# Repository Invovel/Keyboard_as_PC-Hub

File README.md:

# Keyboard as PC Hub

## 当前产品基准 · RevC

[RevC 工程入口](docs/revc/README.md) · [差异审查](docs/revc/REVIEW.md) · [工作分工](docs/revc/PLAN.md) · [协作规范](AGENTS.md)。

冻结环形霍尔四键和独立 RGB、EC56 与独立屏幕下压、承力下壳、双马达、独立麦克风、浮动 USB-C 键盘公头，以及完整 Hub 和隔离口。右 MAG、左拨轮、现有五页固件与可选底置 Dock 继续纳入。现行工程从已核验的 116 封装修复板继承，当前保存板有 159 个封装。详见[真实四层铜、焊盘和钻孔证据](docs/revc/evidence/README.md)。**制造未放行。**

### RevC PCB 线路综合图

图源为保存板 `942accd835ab9017…`。内层覆铜另见[电源与地平面](docs/revc/evidence/PC_Hub_Inner_Planes.svg)。[查看 SVG 原图](docs/revc/evidence/PC_Hub_Pure_Circuit_Overview.svg) · [MAG-R 修改进度](docs/revc/pcb/MAG_R_PROGRESS.md)。

## R3.1 历史设计资料

**Desktop Control Hub · R3.1：Core＋可选下置Power Dock＋低功耗MAG附件。**

Core背部PC-C是唯一电脑上行，单线从电脑允许的VBUS预算取电，目标为不依赖Dock即可使用主体与键盘。Hub硬件转发USB外设数据，ESP32负责圆屏、旋钮、四键、音频和HID；Hub启动不应依赖ESP32固件。单线功耗、Hub配置与故障独立性尚未通过整机验证。

[R3.1 交接](docs/R3_1_CODEX_HANDOFF.md) · [历史差异与决策](docs/R3_1_DECISIONS.md) · [WP1/WP2 工程评审](docs/R3_1_ENGINEERING_REVIEW.md) · [当前开发入口](CODEX_START.md)

[补充讨论采用/放弃清单](docs/R3_1_SUPPLEMENT.md)：保留五键与104mm前部横条，补强Hub启动和Slider验证，早期双向供电/竖条/第二上行不混入当前设计。

**新增设计决定：[最右侧 ISO／DEBUG USB-A](docs/iso-debug-r3-1.md)。** PC-C候选中心移至X≈+64，ISO口X≈+91；由P6经独立USB2双下游Hub保留CTRL并增设隔离调试链路。首版采用隔离电源、集成限流/短路/防反灌保护、数据ESD和本地故障指示；精确计量留作后续选装。[候选材料表](hardware/electronics/iso-debug-candidate-bom.csv)不等于采购或保护能力认证。

[原理图摆位表](docs/iso-debug-schematic-placement-r3-1.md) · [A3摆位视图](design/drawings/iso-debug-schematic-placement-r3-1.svg) · [首版功能连接参考](design/drawings/iso-debug-minimal-schematic-r3-1.svg) · [Anatomy结构视图](design/visualization/iso-debug-anatomy.html) · [预览图](design/visualization/iso-debug-anatomy-preview.png)。当前仅确定原理图页内位置，未画导线或PCB；现有KiCad主工程尚未写入该页。

## R3.1 结构与接口

| 部位 | R3.1分工 |
| --- | --- |
| Core背部 | A1、A2、PC-C、最右侧ISO／DEBUG USB-A；PC-C唯一电脑上行，无Core POWER输入 |
| Core左侧 | FAST-C，目标10Gbps下游；实际供电按预算，不预先承诺3A |
| KBD / CTRL | 可调Type-C键盘公头 / 内部ESP32 USB2 Full-Speed HID |
| Core底部 | P4 Dock DATA＋独立PWR/CTRL预留，封装与开孔未定 |
| 可选下置Dock | Rev B：扩展Hub、外部PD受电、保护降压、单向给Core供电；没有第二电脑上行 |
| 两端MAG | 低速、低功耗8触点；五键及前部唯一横向触控条，不传高速USB/全机电流 |

逻辑下游P1=A1、P2=A2、P3=FAST、P4=DOCK、P5=KBD、P6=USB2分支至原CTRL与新ISO／DEBUG；这是架构分配，不是芯片物理引脚。USB7206C仍为候选，尚未证明Core单线工作能力。旧A3迁为Dock数据链路，POWER IN移至Dock；旧100W/46W单体预算仅保留为历史。

| 尺寸 | 候选值，mm |
| --- | --- |
| Core / PCB | 228×76、5°，前20/后26.65；PCB216×64×1.6 |
| 短四键 | 四片镜像，外端X=±84，两端各留30固定壳面；键面高0.3 |
| 感应中心 | (±65,±18)，保持原位 |
| 环 / 屏 / AA | Ø60 / Ø44.32 / Ø38.16；单边可见边框1.8 |
| 五键 / 横条 | 112×76一字五键；前部横条104×22×8，目标有效长90～96 |
| 底部Dock研究区 | 48×18功能区；8板间距和20高Dock包络均未冻结 |

新增[左右马达预留与PCB布局](hardware/pcb/references/core-haptic-placement-r3-1.md)：2026-10-22锁定[iPhone 7 Plus Taptic Engine](docs/haptic-iphone-7-plus.md)，按用户给定含耳50×12.5×2.6 mm设计，每侧装配区改为15×54×6 mm、长边沿Y，两端顶面保持完整留白。接线采用六测试焊盘最外侧两点接独立触觉驱动；[本轮原生执行记录](hardware/pcb/references/haptic-7plus-native-update.md)与[10月19日历史板图/DRC](hardware/pcb/exports/core-r3-1-haptic-study/README.md)分开保存。新板尚未接网/布线，不能打样。

## 原HTML持续更新

[原单文件HTML](design/visualization/hairline-keyboard-hub.html) · [使用与截图](design/visualization/README.md)。下载后离线打开；悬停主体展开、点击固定/复位，右侧五键及横条磁吸拆分。可选Dock只在主体展开时显示研究包络；默认Core不装Dock。GitHub README仅显示静态图。

[底部接口与侧剖](design/drawings/dock-interface-r3-1.svg) · [R3.1机械说明](hardware/enclosure/dimensions-r3-1.md) · [端口选型表](hardware/electronics/dock-port-selection.csv)

[ISO口与右马达、后孔空间关系](design/drawings/iso-debug-rear-study-r3-1.svg)：这是候选二维研究，开孔仍未冻结。

## 实物进展与文件分类

已运行主体：圆屏、触控页面、触摸板、USB键鼠/媒体HID、四键、按压输入、编码器与提示音；[实测历史](docs/body-core-bringup.md)保留原文。Touchpad延迟本轮不改。新增[INMP441代码](docs/microphone-inmp441.md)只编译，默认关闭，未接实物。输入按压通过不代表屏幕Z轴机械机构已完成。

| 分类 | 入口 | 状态 |
| --- | --- | --- |
| 固件 | [firmware](firmware/README.md) | 保留已运行GPIO与整合代码，本轮不改动/烧录 |
| 展示与图纸 | [design](design/README.md) | 原HTML、R3.1俯视/底视/剖面示意 |
| 机械 | [hardware/enclosure](hardware/enclosure/README.md) | R3.1参数/草模，未实体编译与装配验证 |
| PCB | [hardware/pcb](hardware/pcb/README.md) | 新增指定工程的R3.1布局草案与马达预留；未接网/布线，DRC未通过；R3载板保留历史 |
| 接口与接线 | [hardware/electronics](hardware/electronics/README.md) | 新接口目标与既有实物分开记录 |
| 镜像与证据 | [releases](releases/README.md)、[tests](tests/README.md) | 保留原镜像、许可和真实日志 |

尚未完成电源/Hub/Dock电路、连接器冻结、ERC、USB合规、闭壳温升或制造放行。新增布局已运行DRC但未通过；完整原理图与电气连接仍待完成。不做第二上行、双向大电流、手机高压PD输出、读卡、电池或竖触控条。

[目录规则](docs/repository-layout.md) · [本轮检查](tests/design/r3-1-review.md) · [R3历史尺寸](hardware/enclosure/dimensions-r3.md) · [旧单体供电方案](docs/desktop-power-dock.md) · [R2历史](hardware/enclosure/dimensions-r2.md)

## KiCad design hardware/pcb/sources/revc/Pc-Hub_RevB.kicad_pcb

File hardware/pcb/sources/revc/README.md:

# PC-Hub RevC KiCad 工作工程

打开 [Pc-Hub_RevB.kicad_pro](Pc-Hub_RevB.kicad_pro)。保留 KiCad 原文件名以维持工程及层级标识。本项目从 116 封装保存板 `3f082629954bdb488613209f4213198f4b84ce832a26fdd4af76abb786354d88` 派生。工程引用随项目提交的封装和符号库。

产品坐标、当前批次证据和制造门槛见 [RevC 入口](../../../../docs/revc/README.md)。生产投板须经过剩余的电气、几何及实体校验。

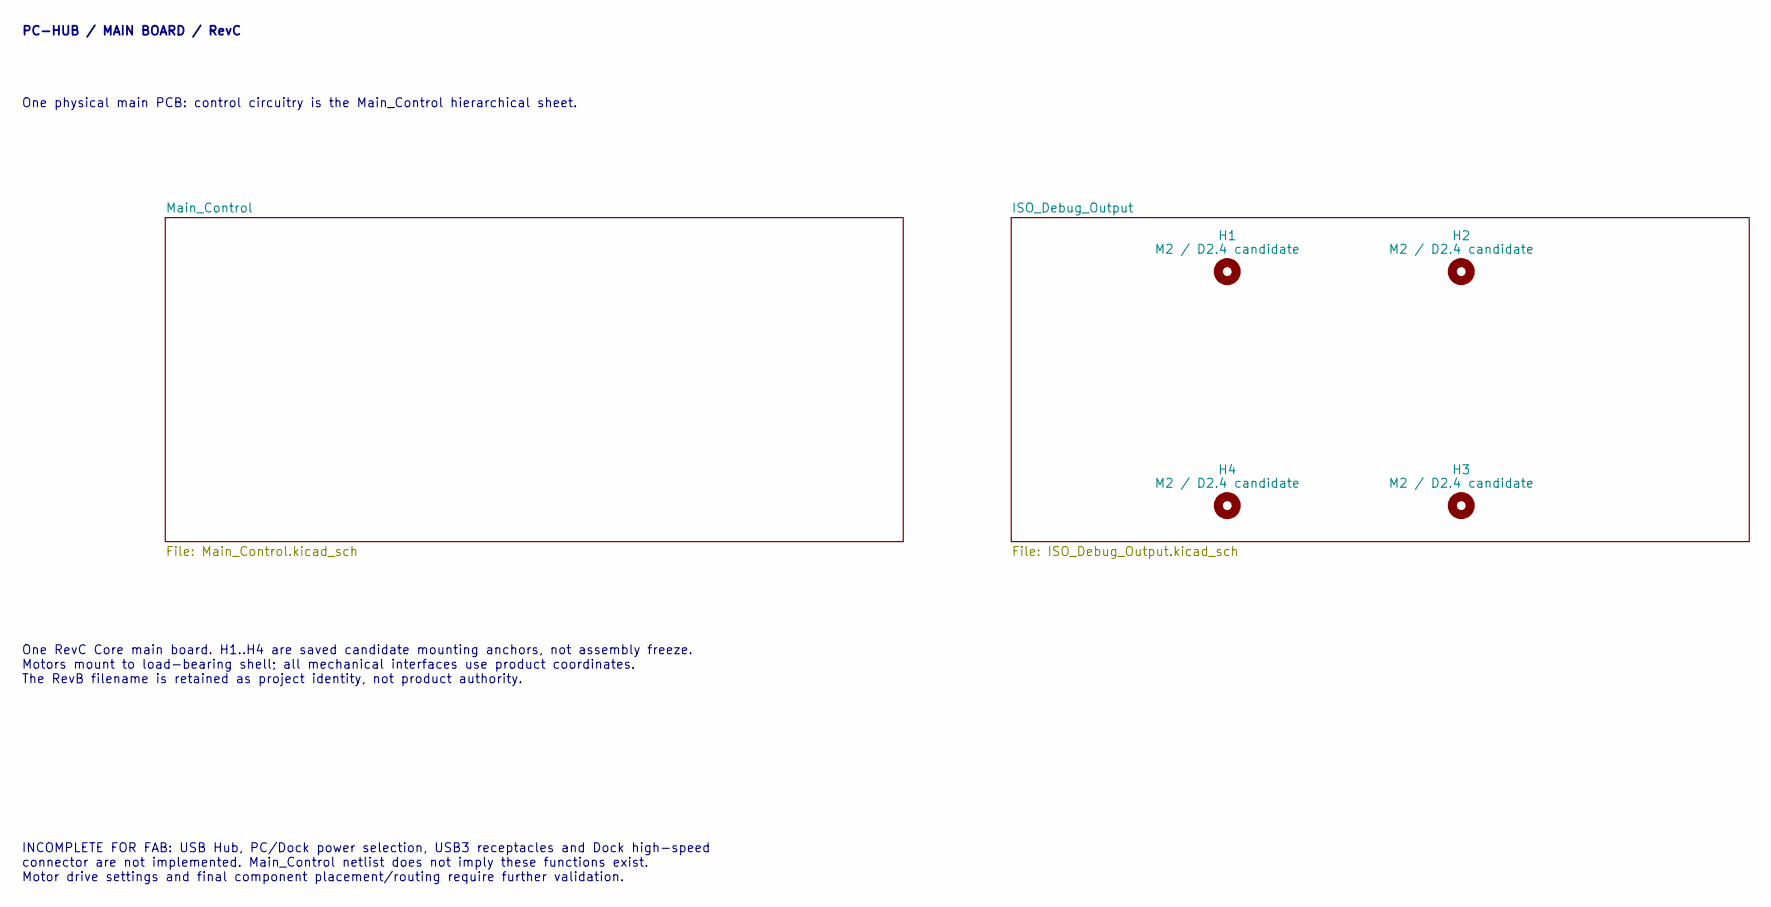
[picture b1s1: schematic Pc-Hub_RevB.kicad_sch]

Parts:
H1: M2 / D2.4 candidate; Core_Frame_With_H1_D2.4
H2, H3, H4: M2 / D2.4 candidate; Hole_D2.4_Keepout5

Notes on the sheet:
One RevC Core main board. H1..H4 are saved candidate mounting anchors, not assembly freeze. Motors mount to load-bearing shell; all mechanical interfaces use product coordinates. The RevB filename is retained as project identity, not product authority.
PC-HUB / MAIN BOARD / RevC
One physical main PCB: control circuitry is the Main_Control hierarchical sheet.
INCOMPLETE FOR FAB: USB Hub, PC/Dock power selection, USB3 receptacles and Dock high-speed connector are not implemented. Main_Control netlist does not imply these functions exist. Motor drive settings and final component placement/routing require further validation.
